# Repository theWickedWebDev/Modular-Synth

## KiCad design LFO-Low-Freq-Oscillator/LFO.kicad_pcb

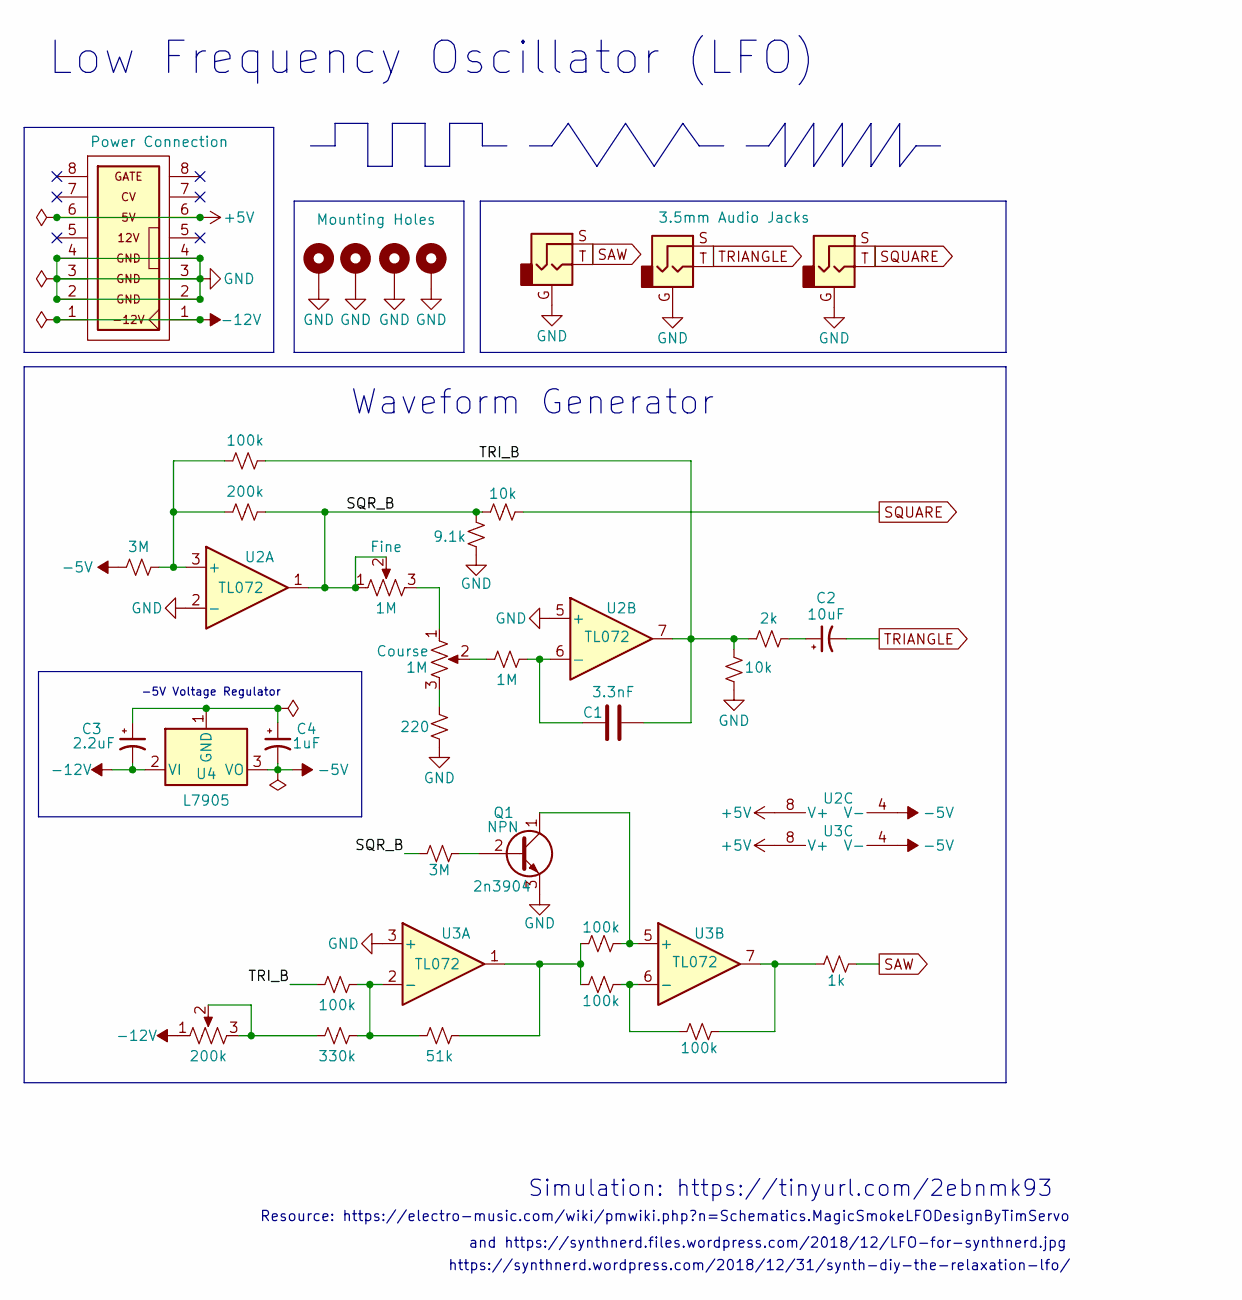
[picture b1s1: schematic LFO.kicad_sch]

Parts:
C1: C; C_Disc_D5.1mm_W3.2mm_P5.00mm
C2: C_Polarized_Small_US; CP_Radial_D6.3mm_P2.50mm
C3, C4: C_Polarized_Small_US; CP_Elec_4x5.4
H1, H2, H3, H4: MountingHole_Pad; MountingHole_3mm_Pad_Via
J1, J2, J3: AudioJack2_Ground; 3.5mm-mono-jack-eurorack-2
Q1: 2n3904; TO-92_Inline
R1, R2, R3, R4, R5, R6, R7, R8, R9, R10, R11, R12, R13, R14, R15, R16, R17: R_Small_US; R_0805_2012Metric
RV1, RV2, RV3: R_Potentiometer_US; alpha-9mm-potentiometer
U1: Eurorack_IDE_16P; IDC-Socket-Eurorack_16p_2.54mm
U2, U3: TL072; SOIC-8_3.9x4.9mm_P1.27mm
U4: L7905; TO-220-3_Vertical

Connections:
+5V: U1.6 (5V), U2.8 (V+), U3.8 (V+)
-5V: C4.2, R1.1, U2.4 (V-), U3.4 (V-), U4.3 (VO)
-12V: C3.2, RV3.1, U1.1 (-12V), U4.2 (VI)
/SQR_B: R3.2, R5.1, R6.1, R12.1, RV1.1, RV1.2, U2.1
/TRI_B: C1.2, R2.2, R8.2, R9.2, R10.1, U2.7
GND: H1.1, H2.1, H3.1, H4.1, J1.G, J2.G, J3.G, Q1.3 (E), R4.1, R5.2, R8.1, U1.2 (GND), U1.3 (GND), U1.4 (GND), U2.2 (-), U2.5 (+), U3.3 (+)
unnamed: C1.1, R7.1, U2.6 (-)
unnamed: C2.1, R9.1
unnamed: C3.1, C4.1, U4.1 (GND)
unnamed: Q1.1 (C), R14.2, U3.5 (+)
unnamed: Q1.2 (B), R12.2
unnamed: R1.2, R2.1, R3.1, U2.3 (+)
unnamed: R4.2, RV2.3
unnamed: R7.2, RV2.2
unnamed: R10.2, R11.2, R13.1, U3.2 (-)
unnamed: R11.1, RV3.2, RV3.3
unnamed: R13.2, R14.1, R15.1, U3.1
unnamed: R15.2, R16.1, U3.6 (-)
unnamed: R16.2, R17.1, U3.7
unnamed: RV1.3, RV2.1
SAW: J1.S, J1.T, R17.2
SQUARE: J3.S, J3.T, R6.2
TRIANGLE: C2.2, J2.S, J2.T

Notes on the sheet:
-5V Voltage Regulator
https://synthnerd.wordpress.com/2018/12/31/synth-diy-the-relaxation-lfo/
Resource: https://electro-music.com/wiki/pmwiki.php?n=Schematics.MagicSmokeLFODesignByTimServo
and https://synthnerd.files.wordpress.com/2018/12/LFO-for-synthnerd.jpg
Waveform Generator
Low Frequency Oscillator (LFO)
Simulation: https://tinyurl.com/2ebnmk93

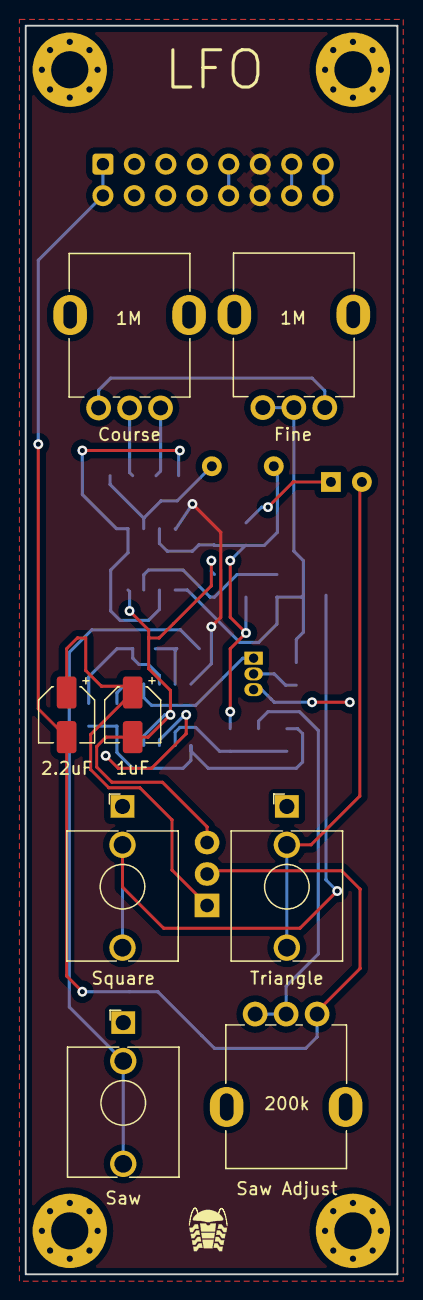
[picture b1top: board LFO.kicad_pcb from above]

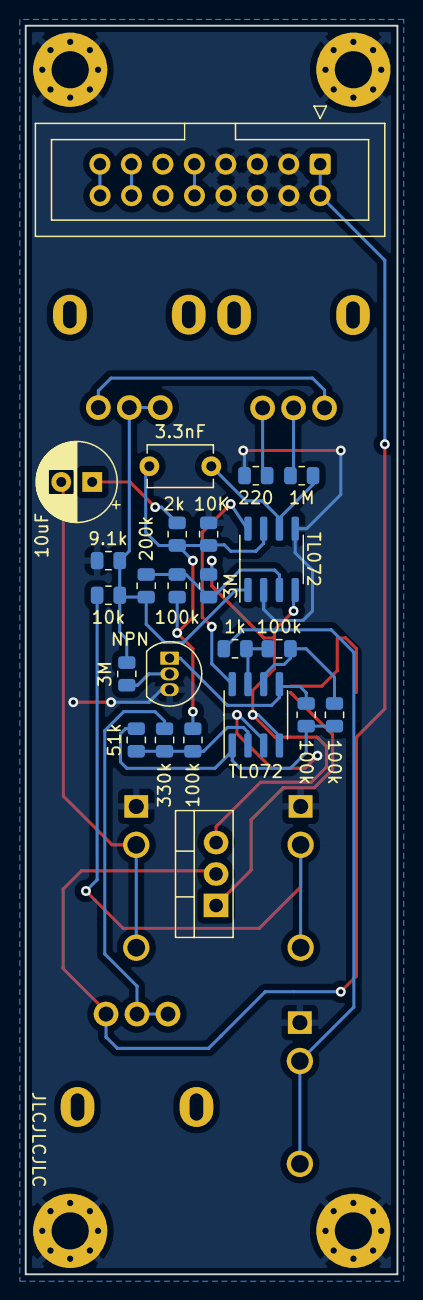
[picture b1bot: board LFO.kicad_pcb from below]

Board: 2 copper layers, 30.0 x 100.8 mm, 36 parts (24 on the bottom side), 23 nets.

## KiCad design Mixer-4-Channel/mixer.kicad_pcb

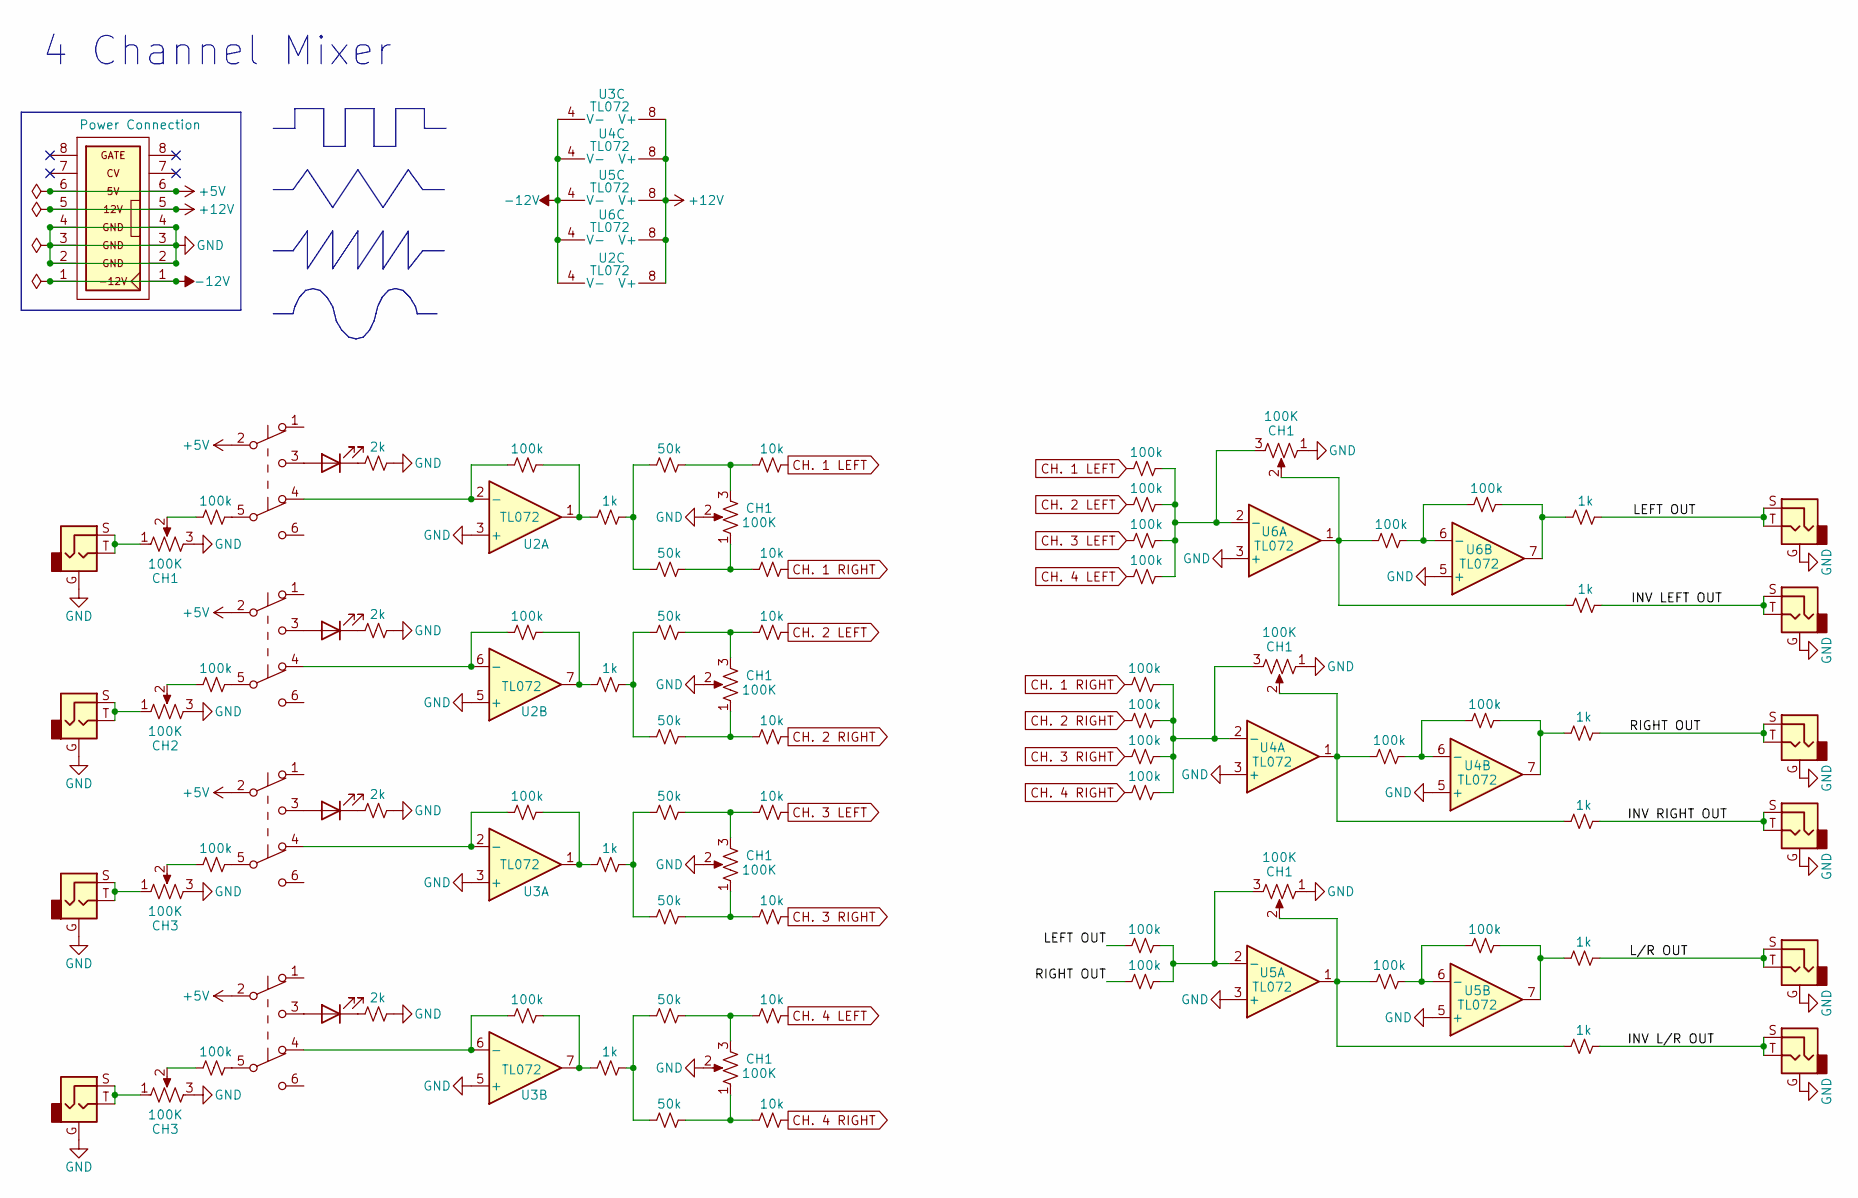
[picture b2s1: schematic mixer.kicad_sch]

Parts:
D1, D2, D3, D4: LED; LED_D3.0mm
J1, J2, J3, J4, J5, J6, J7, J8, J9, J10: AudioJack2_Ground; 3.5mm-mono-jack-eurorack-2
R1, R2, R3, R4, R5, R6, R7, R8, R9, R10, R11, R12, R13, R14, R15, R16, R17, R18, R19, R20, R21, R22, R23, R24, R25, R26, R27, R28, R29, R30, R31, R32, R33, R34, R35, R36, R37, R38, R39, R40, R41, R42, R43, R44, R45, R46, R47, R48, R49, R50, R51, R52, R53, R54: R_Small_US; R_0805_2012Metric
RV1, RV2, RV3, RV4, RV9, RV10, RV11: R_Potentiometer_US; Slide-Potentiometer-30mm-43.5mm
RV5, RV6, RV7, RV8: R_Potentiometer_US; alpha-9mm-potentiometer
SW1, SW2, SW3, SW4: SW_Push_DPDT; DPDT-LatchingSwitch-THT
U1: Eurorack_IDE_16P; IDC-Socket-Eurorack_16p_2.54mm
U2, U3, U4, U5, U6: TL072; SOIC-8_3.9x4.9mm_P1.27mm

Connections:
+5V: SW1.2 (B), SW2.2 (B), SW3.2 (B), SW4.2 (B), U1.6 (5V)
+12V: U1.5 (12V), U2.8 (V+), U3.8 (V+), U4.8 (V+), U5.8 (V+), U6.8 (V+)
-12V: U1.1 (-12V), U2.4 (V-), U3.4 (V-), U4.4 (V-), U5.4 (V-), U6.4 (V-)
/INV LEFT OUT: J6.S, J6.T, R54.1
/INV L/R OUT: J10.S, J10.T, R52.1
/INV RIGHT OUT: J8.S, J8.T, R50.1
/LEFT OUT: J5.S, J5.T, R37.2, R53.1
/L/R OUT: J9.S, J9.T, R51.1
/RIGHT OUT: J7.S, J7.T, R38.2, R49.1
CH. 1 LEFT: R25.1, R39.2
CH. 1 RIGHT: R26.1, R33.2
CH. 2 LEFT: R27.1, R40.2
CH. 2 RIGHT: R28.1, R34.2
CH. 3 LEFT: R29.1, R41.2
CH. 3 RIGHT: R30.1, R35.2
CH. 4 LEFT: R31.1, R42.2
CH. 4 RIGHT: R32.1, R36.2
GND: J1.G, J2.G, J3.G, J4.G, J5.G, J6.G, J7.G, J8.G, J9.G, J10.G, R5.1, R6.1, R7.1, R8.1, RV1.3, RV2.3, RV3.3, RV4.3, RV5.2, RV6.2, RV7.2, RV8.2, RV9.1, RV10.1, RV11.1, U1.2 (GND), U1.3 (GND), U1.4 (GND), U2.3 (+), U2.5 (+), U3.3 (+), U3.5 (+), U4.3 (+), U4.5 (+), U5.3 (+), U5.5 (+), U6.3 (+), U6.5 (+)
unnamed: D1.1 (K), R5.2
unnamed: D1.2 (A), SW1.3 (C)
unnamed: D2.1 (K), R6.2
unnamed: D2.2 (A), SW2.3 (C)
unnamed: D3.1 (K), R7.2
unnamed: D3.2 (A), SW3.3 (C)
unnamed: D4.1 (K), R8.2
unnamed: D4.2 (A), SW4.3 (C)
unnamed: J1.S, J1.T, RV1.1
unnamed: J2.S, J2.T, RV2.1
unnamed: J3.S, J3.T, RV3.1
unnamed: J4.S, J4.T, RV4.1
unnamed: R1.1, SW1.5 (B)
unnamed: R1.2, RV1.2
unnamed: R2.1, SW2.5 (B)
unnamed: R2.2, RV2.2
unnamed: R3.1, SW3.5 (B)
unnamed: R3.2, RV3.2
unnamed: R4.1, SW4.5 (B)
unnamed: R4.2, RV4.2
unnamed: R9.2, SW1.4 (A), U2.2 (-)
unnamed: R10.1, R14.2, U2.7
unnamed: R10.2, SW2.4 (A), U2.6 (-)
unnamed: R11.1, R15.2, U3.1
unnamed: R11.2, SW3.4 (A), U3.2 (-)
unnamed: R12.1, R16.2, U3.7
unnamed: R12.2, SW4.4 (A), U3.6 (-)
unnamed: R13.1, R17.2, R18.2
unnamed: R9.1, R13.2, U2.1
unnamed: R14.1, R19.2, R20.2
unnamed: R15.1, R21.2, R22.2
unnamed: R16.1, R23.2, R24.2
unnamed: R17.1, R25.2, RV5.3
unnamed: R18.1, R26.2, RV5.1
unnamed: R19.1, R27.2, RV6.3
unnamed: R20.1, R28.2, RV6.1
unnamed: R21.1, R29.2, RV7.3
unnamed: R22.1, R30.2, RV7.1
unnamed: R23.1, R31.2, RV8.3
unnamed: R24.1, R32.2, RV8.1
unnamed: R33.1, R34.1, R35.1, R36.1, RV9.3, U4.2 (-)
unnamed: R37.1, R38.1, RV10.3, U5.2 (-)
unnamed: R39.1, R40.1, R41.1, R42.1, RV11.3, U6.2 (-)
unnamed: R43.1, R46.2, U4.6 (-)
unnamed: R43.2, R50.2, RV9.2, U4.1
unnamed: R44.1, R47.2, U5.6 (-)
unnamed: R44.2, R52.2, RV10.2, U5.1
unnamed: R45.1, R48.2, U6.6 (-)
unnamed: R45.2, R54.2, RV11.2, U6.1
unnamed: R46.1, R49.2, U4.7
unnamed: R47.1, R51.2, U5.7
unnamed: R48.1, R53.2, U6.7

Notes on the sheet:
4 Channel Mixer

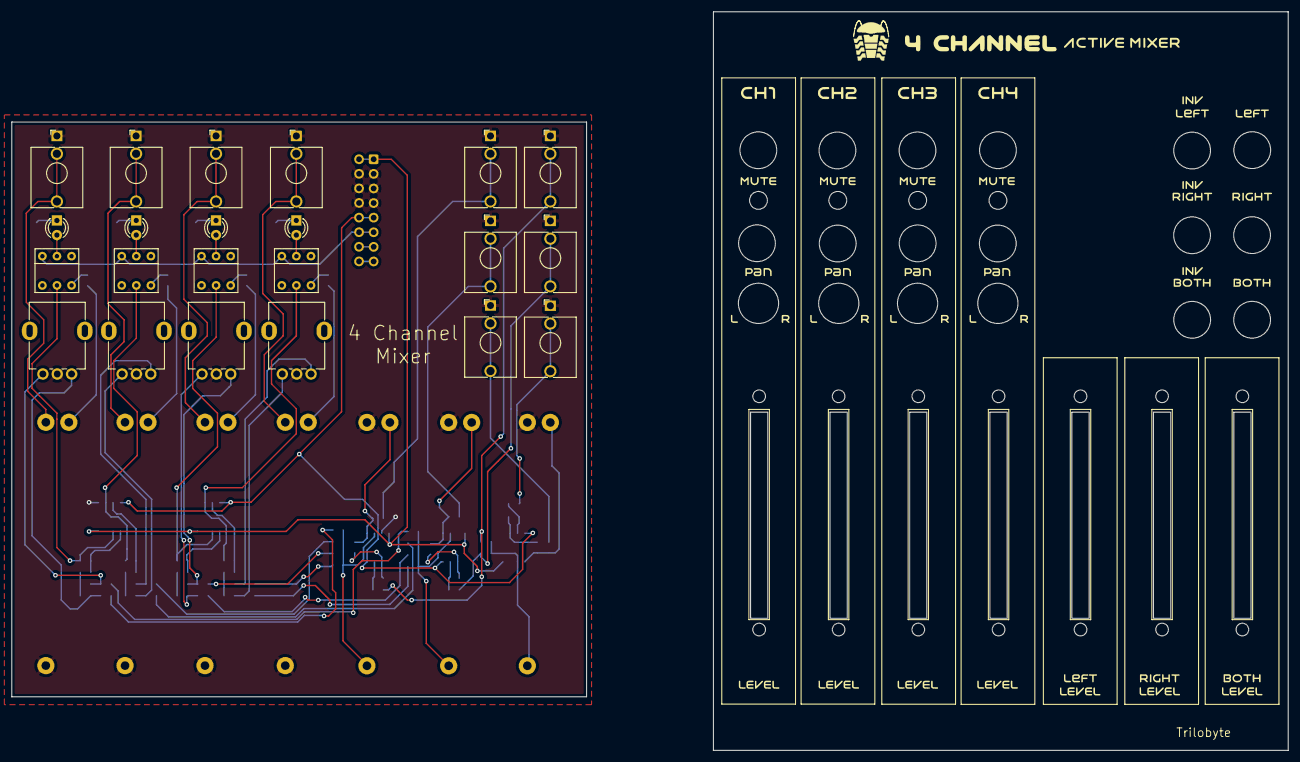
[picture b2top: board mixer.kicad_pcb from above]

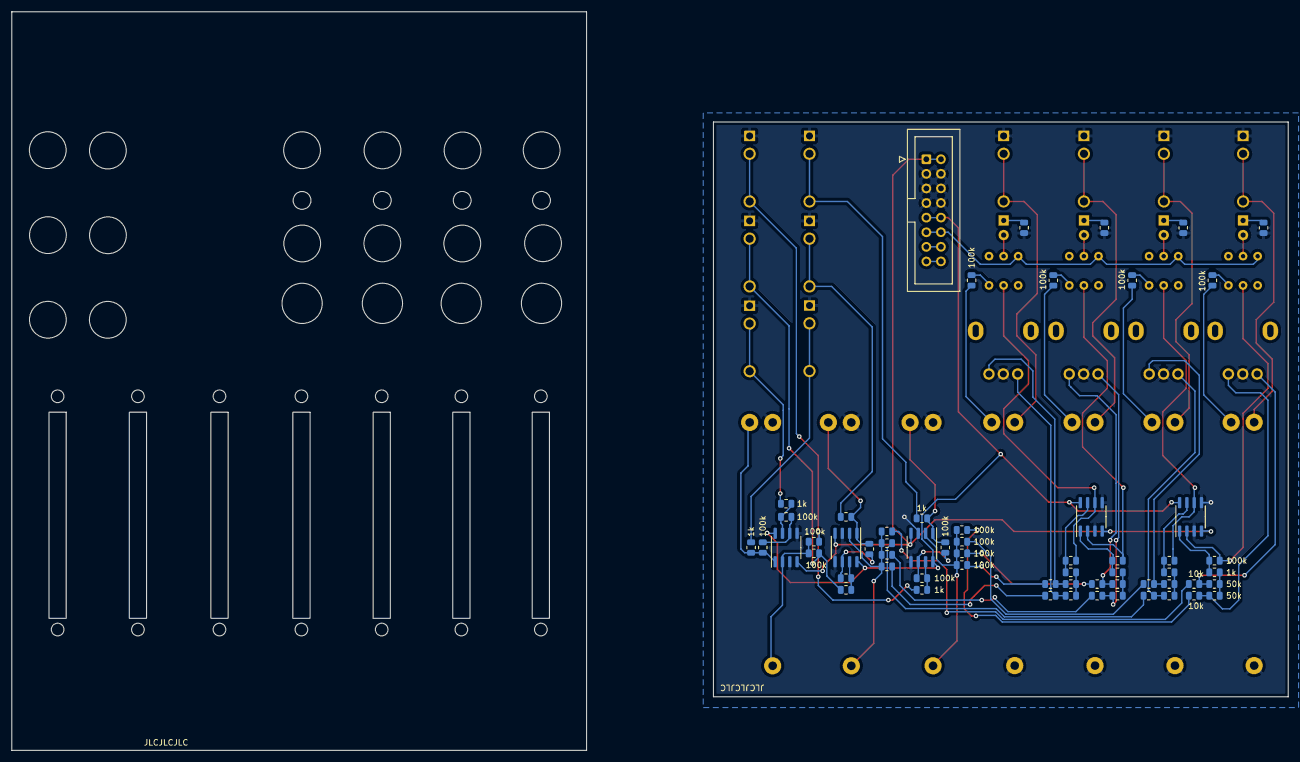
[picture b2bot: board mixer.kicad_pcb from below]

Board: 2 copper layers, 100.0 x 100.0 mm, 93 parts (60 on the bottom side), 70 nets.

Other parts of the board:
H1, H1#2, H1#3, H1#4: MountingHole; 3.2mm-mounting-hole-eurorack

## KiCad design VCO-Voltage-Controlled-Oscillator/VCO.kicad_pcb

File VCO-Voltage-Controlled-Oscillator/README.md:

# NEEDS TO BE UPDATED - NOT WORKING

# Voltage Controlled Oscillator

### Live Simulation - [Falstad](https://tinyurl.com/267pkfxt)

Produces a Square Wave and a Triangle Wave whose frequency can be adjusted with a course and fine tune potentiometer.

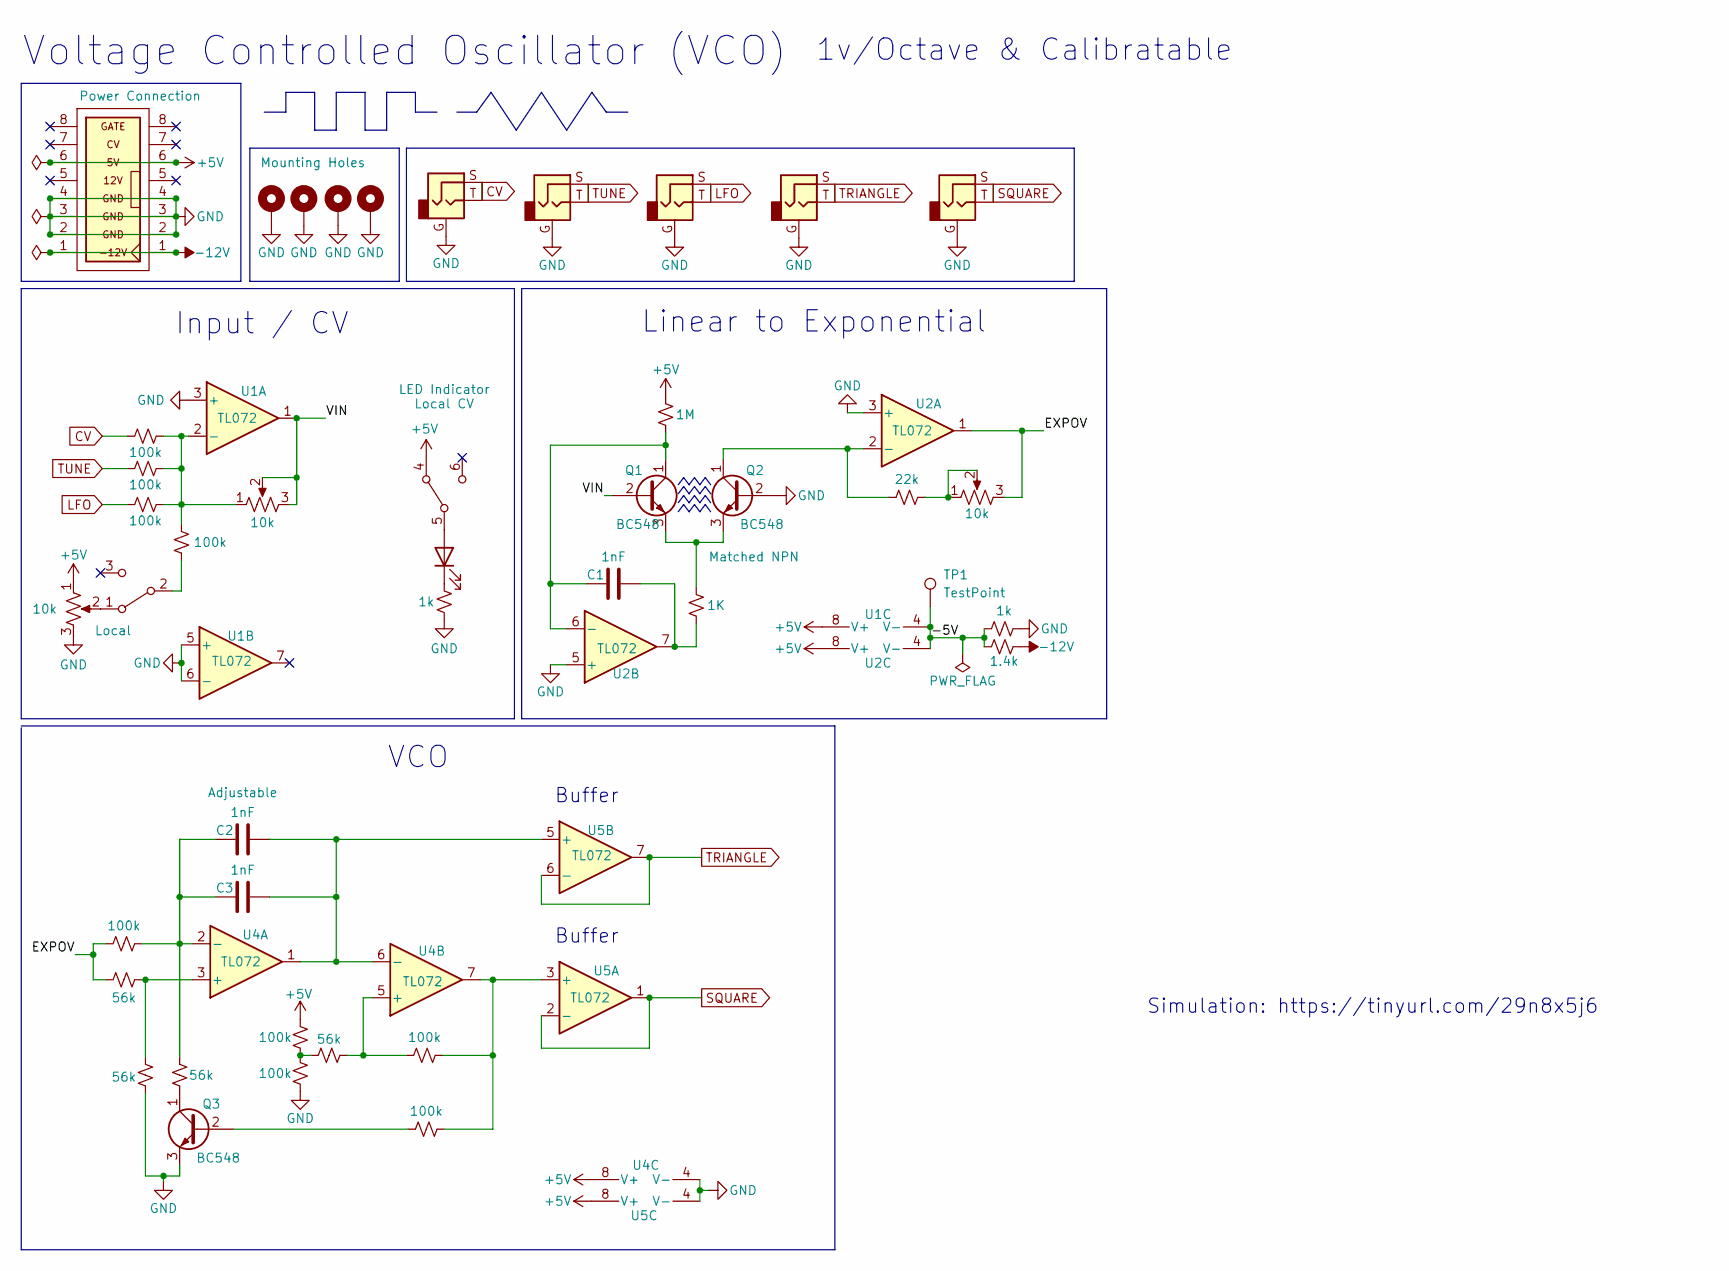
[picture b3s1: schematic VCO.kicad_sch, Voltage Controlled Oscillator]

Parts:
C1: C; C_0805_2012Metric
C2, C3: C; C_Disc_D5.1mm_W3.2mm_P5.00mm
D1: LED; LED_D5.0mm
H1, H2, H3, H4: MountingHole_Pad; MountingHole_3mm_Pad_Via
J1, J2, J3, J4, J5: AudioJack2_Ground; 3.5mm-mono-jack-eurorack-2
Q1, Q2, Q3: BC548; TO-92_Inline
R1, R2, R3, R4, R5, R6, R7, R8, R9, R10, R11, R12, R13, R14, R15, R16, R17, R18, R19: R_Small_US; R_0805_2012Metric
RV1, RV2, RV3: R_Potentiometer_US; alpha-9mm-potentiometer
SW1: SW_DPDT_x2; DPDT-LatchingSwitch-THT
TP1: TestPoint; TestPoint_Keystone_5015_Micro-Minature
U1, U2, U4, U5: TL072; SOIC-8_3.9x4.9mm_P1.27mm
U3: Eurorack_IDE_16P; IDC-Socket-Eurorack_16p_2.54mm

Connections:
+5V: R6.1, R15.2, RV1.1, SW1.4 (A), U1.8 (V+), U2.8 (V+), U3.6 (5V), U4.8 (V+), U5.8 (V+)
-12V: R8.1, U3.1 (-12V)
/-5V: R8.2, R10.2, TP1.1, U1.4 (V-), U2.4 (V-)
/EXPOV: R11.1, R12.1, RV3.3, U2.1
/MANUAL: R5.2, SW1.2 (B)
/VIN: Q1.2 (B), RV2.2, RV2.3, U1.1
CV: J1.S, J1.T, R2.2
GND: H1.1, H2.1, H3.1, H4.1, J1.G, J2.G, J3.G, J4.G, J5.G, Q2.2 (B), Q3.3 (E), R1.2, R10.1, R13.1, R16.1, RV1.3, U1.3 (+), U1.5 (+), U1.6 (-), U2.3 (+), U2.5 (+), U3.2 (GND), U3.3 (GND), U3.4 (GND), U4.4 (V-), U5.4 (V-)
LFO: J3.S, J3.T, R4.2
unnamed: C1.1, Q1.1 (C), R6.2, U2.6 (-)
unnamed: C2.1, C3.1, R11.2, R14.2, U4.2 (-)
unnamed: C2.2, C3.2, U4.1, U4.6 (-), U5.5 (+)
unnamed: D1.1 (K), R1.1
unnamed: D1.2 (A), SW1.5 (B)
unnamed: Q1.3 (E), Q2.3 (E), R7.1
unnamed: Q2.1 (C), R9.1, U2.2 (-)
unnamed: Q3.1 (C), R14.1
unnamed: Q3.2 (B), R19.1
unnamed: R2.1, R3.1, R4.1, R5.1, RV2.1, U1.2 (-)
unnamed: C1.2, R7.2, U2.7
unnamed: R9.2, RV3.1, RV3.2
unnamed: R12.2, R13.2, U4.3 (+)
unnamed: R15.1, R16.2, R17.2
unnamed: R17.1, R18.1, U4.5 (+)
unnamed: R18.2, R19.2, U4.7, U5.3 (+)
unnamed: RV1.2, SW1.1 (A)
SQUARE: J5.S, J5.T, U5.1, U5.2 (-)
TRIANGLE: J4.S, J4.T, U5.6 (-), U5.7
TUNE: J2.S, J2.T, R3.2

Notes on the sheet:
VCO
Voltage Controlled Oscillator (VCO)
Buffer
Input / CV
Linear to Exponential
1v/Octave & Calibratable
Simulation: https://tinyurl.com/29n8x5j6

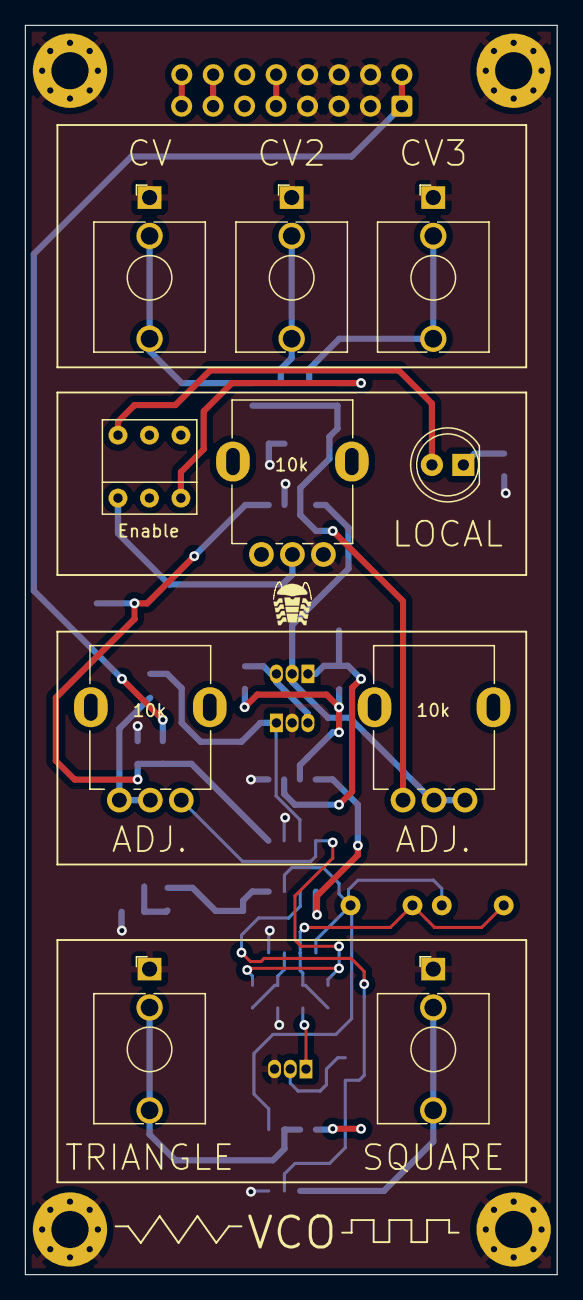
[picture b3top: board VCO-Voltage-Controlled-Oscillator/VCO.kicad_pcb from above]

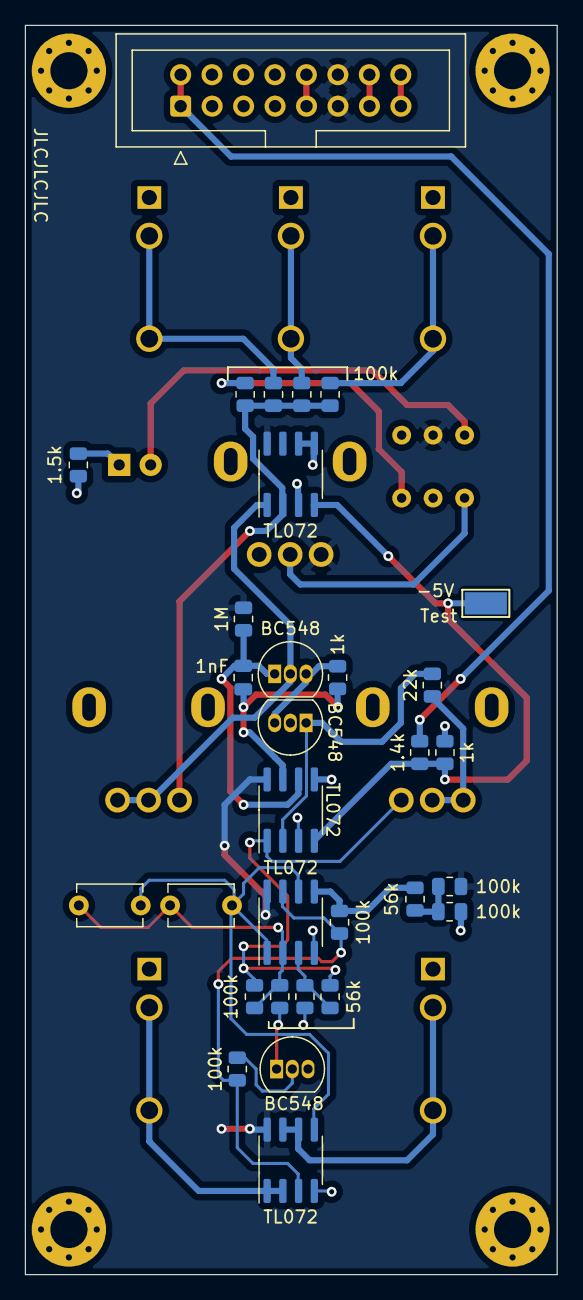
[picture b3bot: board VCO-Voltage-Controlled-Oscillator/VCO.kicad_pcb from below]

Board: 2 copper layers, 42.9 x 100.8 mm, 45 parts (31 on the bottom side), 29 nets.

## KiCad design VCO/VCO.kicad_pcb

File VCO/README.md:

# Voltage Controlled Oscillator

### Live Simulation - [Falstad](https://tinyurl.com/267pkfxt)

Produces a Square Wave and a Triangle Wave whose frequency can be adjusted with a course and fine tune potentiometer.

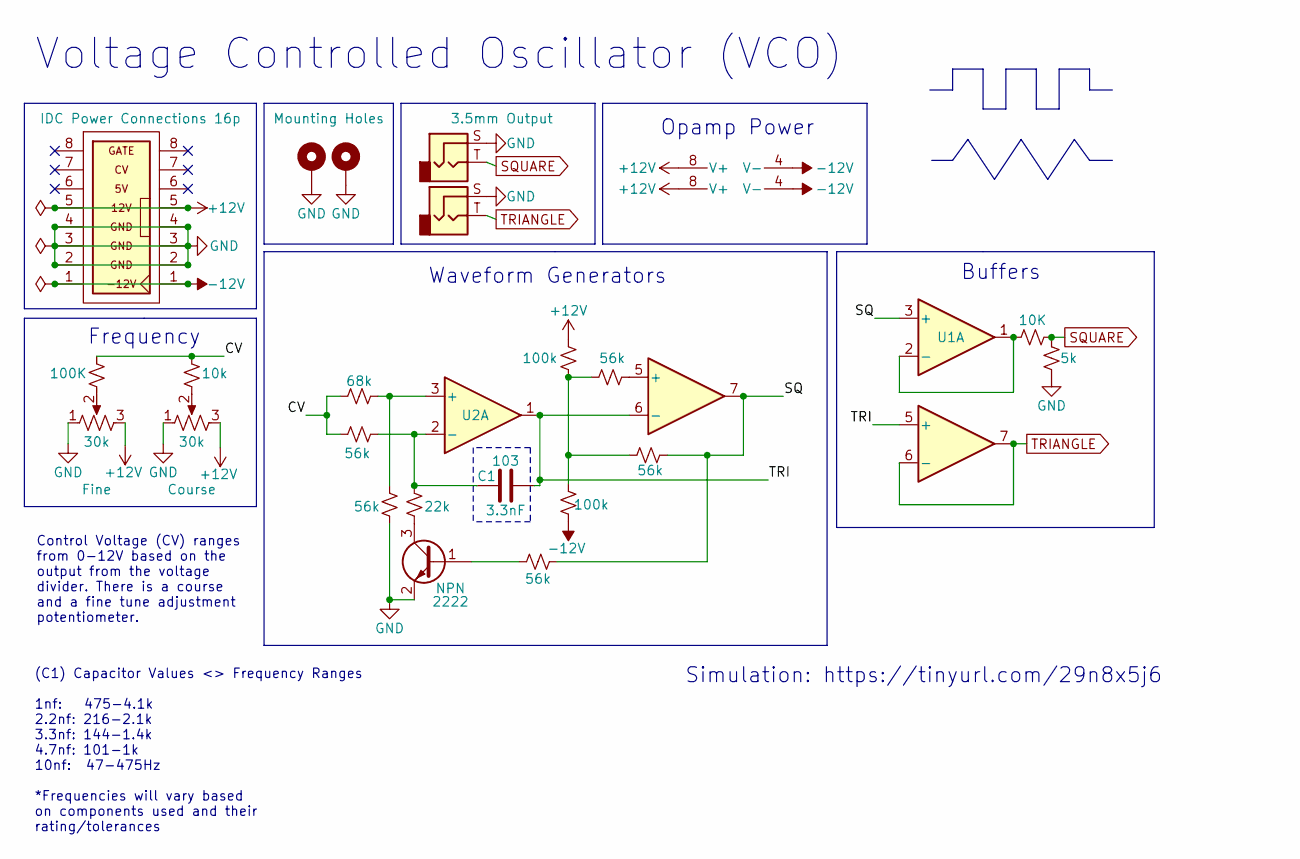
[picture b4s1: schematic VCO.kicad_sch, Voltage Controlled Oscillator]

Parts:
C1: C; C_0805_2012Metric
H1, H2: MountingHole_Pad; MountingHole_3mm_Pad_Via
J2, J3: AudioJack2; ACJS-MV35-3S-audio-jack
Q1: 2N2222_smd-stephen; SOT-23
R1, R2, R4, R5, R6, R7, R8, R9, R10, R11, R12, R13: R_Small_US; R_0805_2012Metric
R3: R_Small_US; R_0805_2012Metric-10K
RV1, RV2: R_Potentiometer_US; Potentiometer_Omeg_PC16BU_Vertical
U1, U2: MC1458; SOIC-8_3.9x4.9mm_P1.27mm
U3: Eurorack_IDE_16P; IDC-Socket-Eurorack_16p_2.54mm

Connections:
+12V: R8.2, RV1.3, RV2.3, U1.8 (V+), U2.8 (V+), U3.5 (12V)
-12V: R9.1, U1.4 (V-), U2.4 (V-), U3.1 (-12V)
/CV: R1.1, R2.2, R3.2, R4.1
/SQ: R7.1, R11.1, U1.3 (+), U2.7
/TRI: C1.2, U1.5 (+), U2.1, U2.6 (-)
GND: H1.1, H2.1, J2.S, J3.S, Q1.2 (E), R5.1, R13.2, RV1.1, RV2.1, U3.2 (GND), U3.3 (GND), U3.4 (GND)
unnamed: C1.1, R4.2, R6.2, U2.2 (-)
unnamed: Q1.1 (B), R7.2
unnamed: Q1.3 (C), R6.1
unnamed: R1.2, R5.2, U2.3 (+)
unnamed: R2.1, RV1.2
unnamed: R3.1, RV2.2
unnamed: R10.1, U2.5 (+)
unnamed: R8.1, R9.2, R10.2, R11.2
unnamed: R12.2, U1.1, U1.2 (-)
SQUARE: J2.T, R12.1, R13.1
TRIANGLE: J3.T, U1.6 (-), U1.7

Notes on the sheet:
Voltage Controlled Oscillator (VCO)
(C1) Capacitor Values <> Frequency Ranges 1nf: 475-4.1k 2.2nf: 216-2.1k 3.3nf: 144-1.4k 4.7nf: 101-1k 10nf: 47-475Hz *Frequencies will vary based on components used and their rating/tolerances
Waveform Generators
Control Voltage (CV) ranges from 0-12V based on the output from the voltage divider. There is a course and a fine tune adjustment potentiometer.
Buffers
Frequency
Opamp Power
Simulation: https://tinyurl.com/29n8x5j6

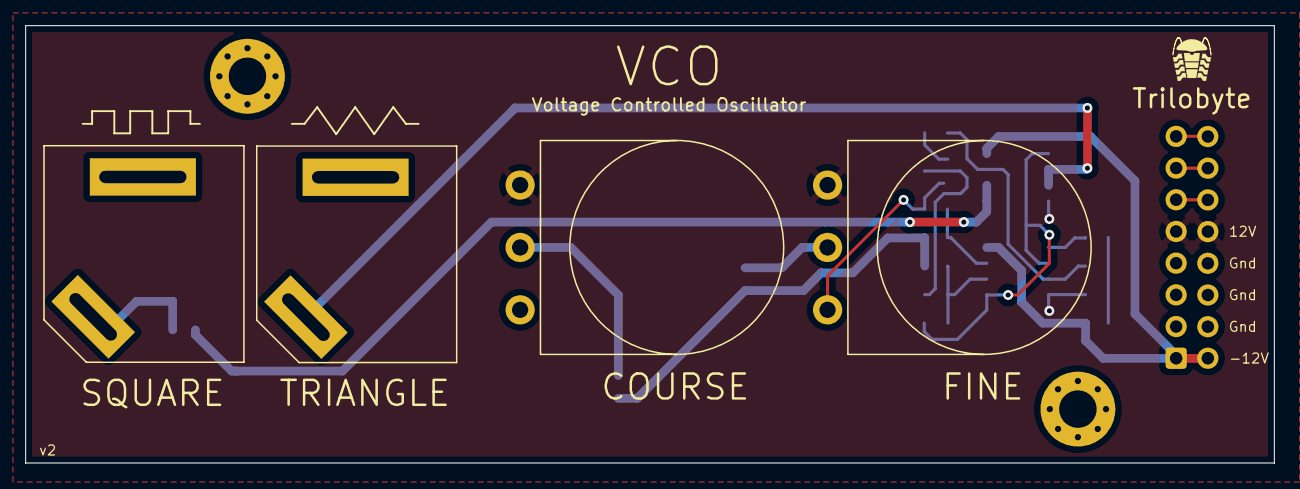
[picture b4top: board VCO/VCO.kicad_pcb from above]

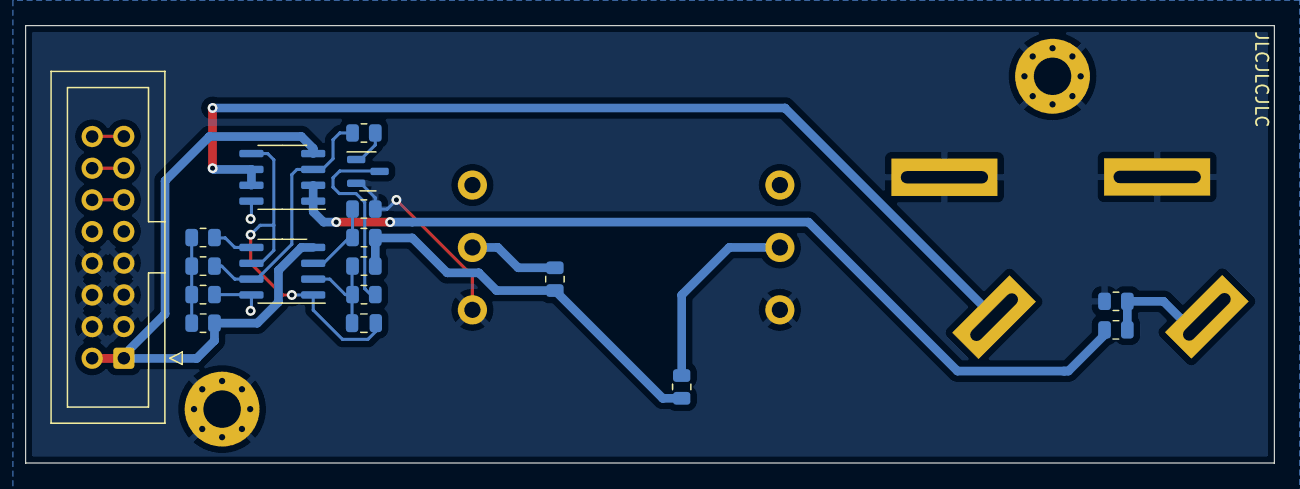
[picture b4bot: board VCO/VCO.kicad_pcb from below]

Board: 2 copper layers, 100.1 x 35.1 mm, 24 parts (18 on the bottom side), 17 nets.

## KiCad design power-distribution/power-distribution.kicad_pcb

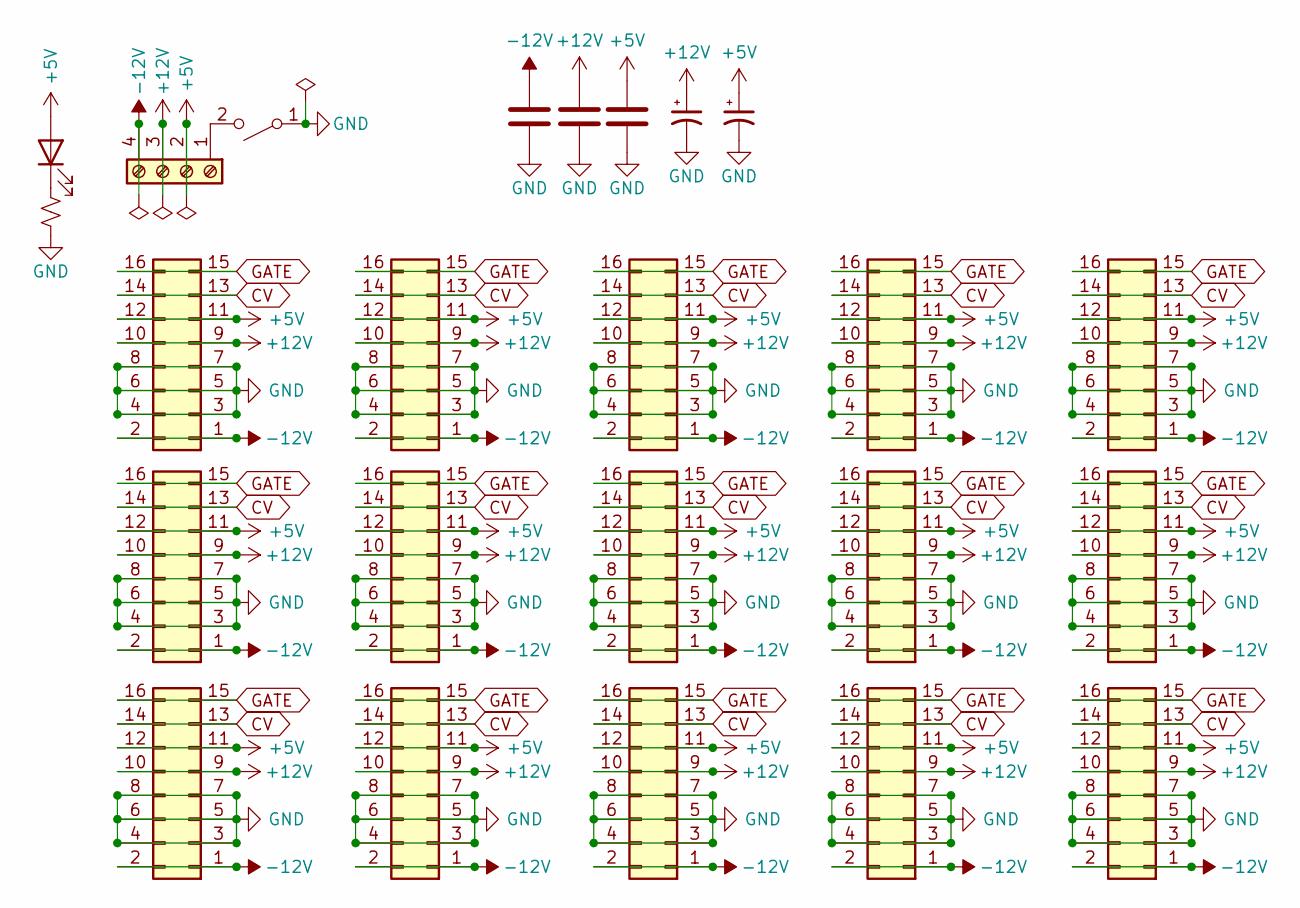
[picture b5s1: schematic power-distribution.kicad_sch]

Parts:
C2, C6: C_Polarized_Small_US; CP_Elec_6.3x7.7
C3, C4, C5: C; C_0805_2012Metric
J1, J2, J3, J4, J5, J6, J7, J8, J9, J10, J11, J12, J14, J15, J16: Conn_02x20_Odd_Even; IDC-Header_2x08_P2.54mm_Vertical
J13: Screw_Terminal_01x04; TerminalBlock_Phoenix_MKDS-1,5-4-5.08_1x04_P5.08mm_Horizont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
SW1: SW_SPST; PinHeader_1x02_P2.54mm_Vertical

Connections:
+5V: C5.1, C6.1, J1.11, J1.12, J2.11, J2.12, J3.11, J3.12, J4.11, J4.12, J5.11, J5.12, J6.11, J6.12, J7.11, J7.12, J8.11, J8.12, J9.11, J9.12, J10.11, J10.12, J11.11, J11.12, J12.11, J12.12, J13.2, J14.11, J14.12, J15.11, J15.12, J16.11, J16.12; also elsewhere on the board
+12V: C2.1, C4.1, J1.9, J1.10, J2.9, J2.10, J3.9, J3.10, J4.9, J4.10, J5.9, J5.10, J6.9, J6.10, J7.9, J7.10, J8.9, J8.10, J9.9, J9.10, J10.9, J10.10, J11.9, J11.10, J12.9, J12.10, J13.3, J14.9, J14.10, J15.9, J15.10, J16.9, J16.10
-12V: C3.1, J1.1, J1.2, J2.1, J2.2, J3.1, J3.2, J4.1, J4.2, J5.1, J5.2, J6.1, J6.2, J7.1, J7.2, J8.1, J8.2, J9.1, J9.2, J10.1, J10.2, J11.1, J11.2, J12.1, J12.2, J13.4, J14.1, J14.2, J15.1, J15.2, J16.1, J16.2
CV: J1.13, J1.14, J2.13, J2.14, J3.13, J3.14, J4.13, J4.14, J5.13, J5.14, J6.13, J6.14, J7.13, J7.14, J8.13, J8.14, J9.13, J9.14, J10.13, J10.14, J11.13, J11.14, J12.13, J12.14, J14.13, J14.14, J15.13, J15.14, J16.13, J16.14
GATE: J1.15, J1.16, J2.15, J2.16, J3.15, J3.16, J4.15, J4.16, J5.15, J5.16, J6.15, J6.16, J7.15, J7.16, J8.15, J8.16, J9.15, J9.16, J10.15, J10.16, J11.15, J11.16, J12.15, J12.16, J14.15, J14.16, J15.15, J15.16, J16.15, J16.16
GND: C2.2, C3.2, C4.2, C5.2, C6.2, J1.3, J1.4, J1.5, J1.6, J1.7, J1.8, J2.3, J2.4, J2.5, J2.6, J2.7, J2.8, J3.3, J3.4, J3.5, J3.6, J3.7, J3.8, J4.3, J4.4, J4.5, J4.6, J4.7, J4.8, J5.3, J5.4, J5.5, J5.6, J5.7, J5.8, J6.3, J6.4, J6.5, J6.6, J6.7, J6.8, J7.3, J7.4, J7.5, J7.6, J7.7, J7.8, J8.3, J8.4, J8.5, J8.6, J8.7, J8.8, J9.3, J9.4, J9.5, J9.6, J9.7, J9.8, J10.3, J10.4, J10.5, J10.6, J10.7, J10.8, J11.3, J11.4, J11.5, J11.6, J11.7, J11.8, J12.3, J12.4, J12.5, J12.6, J12.7, J12.8, J14.3, J14.4, J14.5, J14.6, J14.7, J14.8, J15.3, J15.4, J15.5, J15.6, J15.7, J15.8, J16.3, J16.4, J16.5, J16.6, J16.7, J16.8, SW1.1 (A); also elsewhere on the board
unnamed: J13.1, SW1.2 (B)

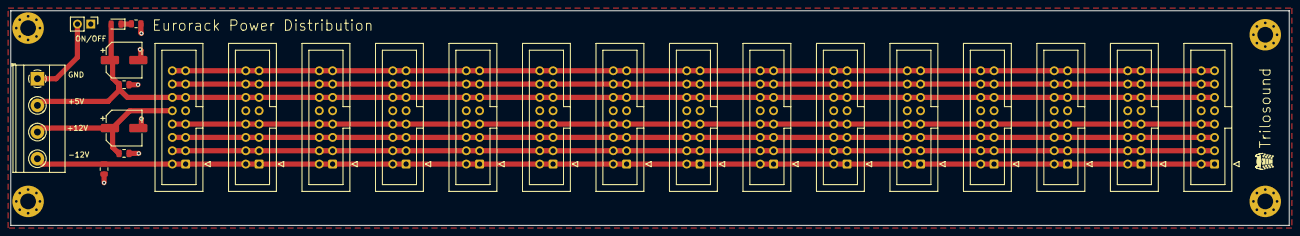
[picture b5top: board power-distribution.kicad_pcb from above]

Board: 2 copper layers, 243.6 x 40.9 mm, 24 parts (0 on the bottom side), 8 nets.

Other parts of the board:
D1: LED; LED_0805_2012Metric-Blue
R1: R_Small_US; R_0805_2012Metric

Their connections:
+5V: D1.2 (A); also elsewhere on the board
GND: R1.2; also elsewhere on the board
unnamed: D1.1 (K), R1.1
